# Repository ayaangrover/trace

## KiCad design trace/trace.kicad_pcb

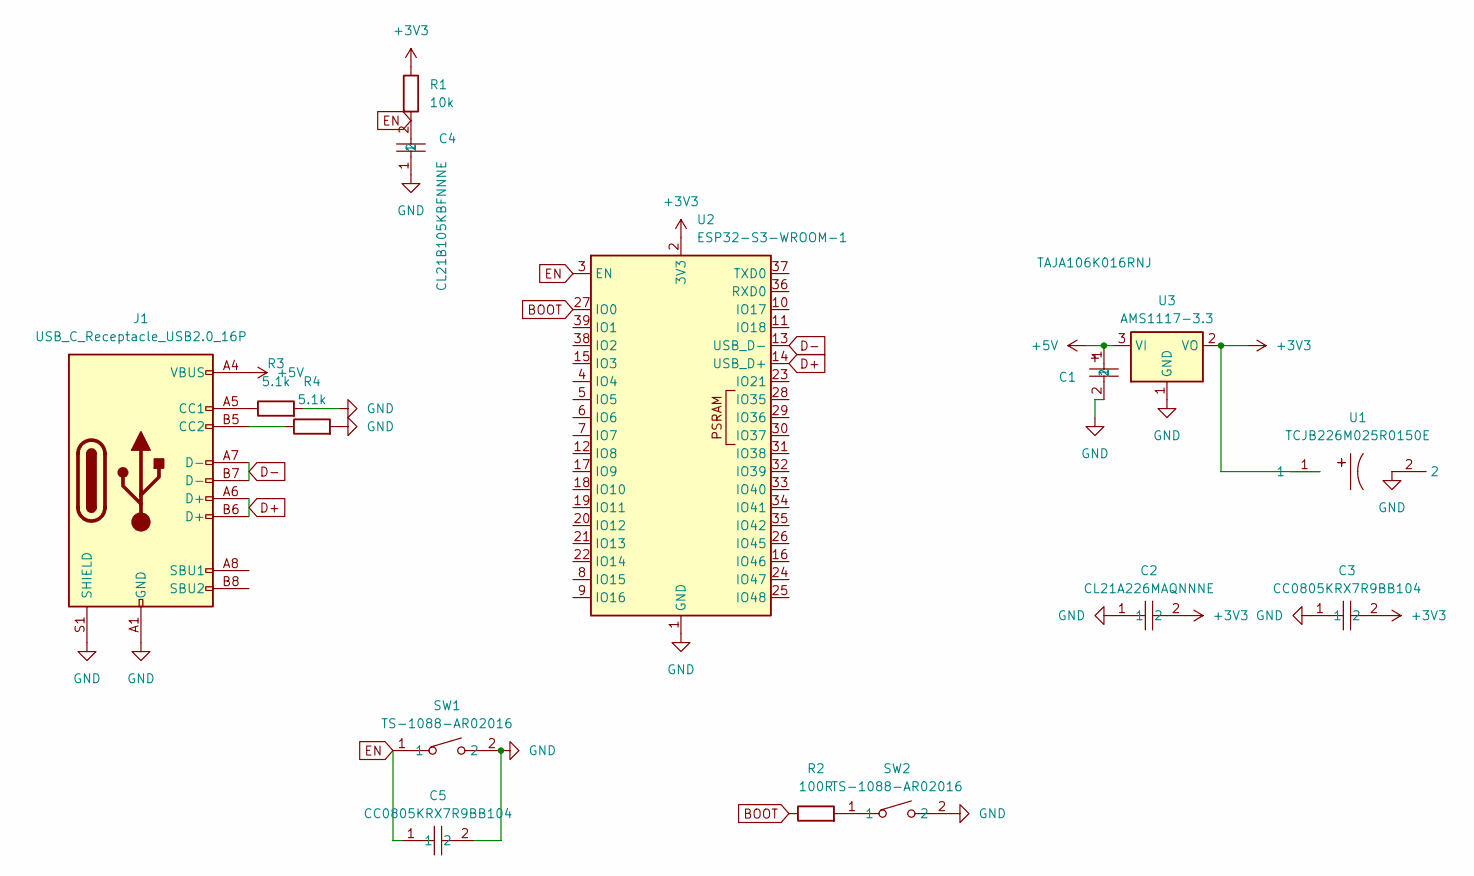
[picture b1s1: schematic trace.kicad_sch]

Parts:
C1: TAJA106K016RNJ; CAP-SMD_L3.2-W1.6-RD-C7171; LCSC Part C7171
C2: CL21A226MAQNNNE; C0805; LCSC Part C45783
C3, C5: CC0805KRX7R9BB104; C0805; LCSC Part C49678
C4: CL21B105KBFNNNE; C0805; LCSC Part C28323
J1: USB_C_Receptacle_USB2.0_16P; USB_C_Receptacle_GCT_USB4105-xx-A_16P_TopMnt_Horizontal
R1: 10k; R_0805_2012Metric
R2: 100R; R_0805_2012Metric
R3, R4: 5.1k; R_0805_2012Metric
SW1, SW2: TS-1088-AR02016; SW-SMD_L3.9-W3.0-P4.45; LCSC Part C720477
U1: TCJB226M025R0150E; CAP-SMD_L3.5-W2.8-FD; LCSC Part C2160823
U2: ESP32-S3-WROOM-1
U3: AMS1117-3.3; SOT-223-3_TabPin2

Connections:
+3V3: C2.2, C3.2, R1.1, U1.1, U2.2 (3V3), U3.2 (VO)
+5V: C1.1, J1.A4 (VBUS), J1.A9 (VBUS), J1.B4 (VBUS), J1.B9 (VBUS), U3.3 (VI)
BOOT: R2.1, U2.27 (IO0)
D+: J1.A6 (D+), J1.B6 (D+), U2.14 (USB_D+)
D-: J1.A7 (D-), J1.B7 (D-), U2.13 (USB_D-)
EN: C4.2, C5.1, R1.2, SW1.1, U2.3 (EN)
GND: C1.2, C2.1, C3.1, C4.1, C5.2, J1.A1 (GND), J1.A12 (GND), J1.B1 (GND), J1.B12 (GND), J1.S1 (SHIELD), R3.2, R4.2, SW1.2, SW2.2, U1.2, U2.1 (GND), U2.40 (GND), U2.41 (GND), U3.1 (GND)
unnamed: J1.A5 (CC1), R3.1
unnamed: J1.B5 (CC2), R4.1
unnamed: R2.2, SW2.1

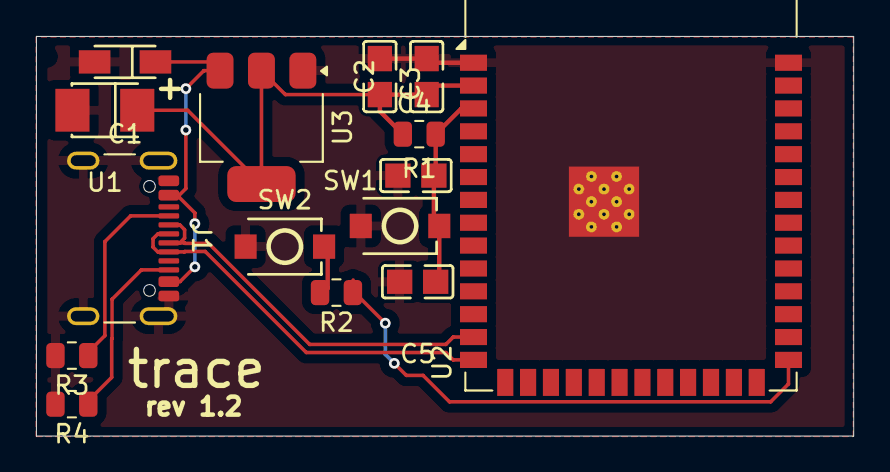
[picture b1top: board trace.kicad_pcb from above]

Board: 2 copper layers, 45.4 x 22.2 mm, 15 parts (0 on the bottom side), 10 nets.

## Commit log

2025-07-02 v1.2
